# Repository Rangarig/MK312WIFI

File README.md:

# MK312 Wifi Bridge

This Project is a replacement for the bluetooth module used on the MK312BT and is based on the ESP8266-01S. This was created at first because the bluetooth interface could not be accessed in a convenient way on a VR headset, but also because of a general lack of reliability of the link. As usual no guarantees can be given, and also if you use this to injure yourself, no responsibility can be taken. This project is a collaboration between Rangarig and cLx. Some code has been imported back from [timdev](https://github.com/timduru/MK312WIFI/commits/timdev/) branch.

## Contents
| Directory      | Contains
|----------------|-------------------------------------------------------------------------|
| MK312Wifi      | Firmware that should be used to flash the ESP (ino source and bin file) |
| MK312-wifi-pcb | Schematics and board KiCad files needed to produce the PCB              |
| DotNetClient   | Example implementation in .net (visual studio code)                     |

## General
This WiFi interface is pin to pin compatible to the bluetooth interface, and designed to be an easier way to make custom implementations of the communication with the MK312 powerbox.
Included is an example C# implementation, that can be used in a unity project. Most existing implementations should be really easy to adapt to this WiFi version.

To make things configuration free the firmware replies to specific broadcast UDP packet, so the software can automatically determine the IP address of the interface.
A single TCP port is used for the actual communication with the device. At any time, only one client can be connected. You can also use the web interface for simple control.

You can see a connection by the radio LED lighting up and then flashing as communication is in progress.

## Hardware
Feel free to use the provided PCB layout for the connections. In case you want to build your own:
Keep in mind that the VCC from the box is 5 volts, so you will need to convert that to 3.3V or you will burn your ESP module.
The signal level from the box is already at 3.3 volts (as there is already a resistor bridge) so we don't really need to do anything else.

Connections are:

| ESP Pin Name | In-between            | MK312 |
|--------------|-----------------------|-------|
| GND          |                       | GND   |
| VCC          | 3.3V regulator        | VCC   |
| CHIP_EN      |                       |       |
| GPIO0        |                       | TX    |
| GPIO2        |                       | RX    |
| GPIO1        | NPN transistor        | STATE |
| GPIO3        | AP mode switch to GND |       |

The hardware serial port outputs a lot of garbage in the bootloader, that can confuse the MK312, so a software implementation is used that might make the used pin seem a bit odd.

## Firmware
Upon first powerup, the device will go into an Access Point mode (the MK312 display will show "WifiAP"), and you can connect to with your cellphone to configure the connection to your local wifi network. Once a WiFi connection is established, the device will display the IP obtained IP address on the LCD display. In consequent powerups the device will reconnect to the same wifi network. If you wish to change the network to use, press the config wifi button. The WifiAP mode is also automatically called if the configured network is not found after power up.

The firmware will negotiate a key with the box, and then use that key continuously internally.
You can send a UDP broadcast to port 8842 containing the string "MK312-ICQ" to have the device return its IP address.
You can then create a TCP connection to that IP Address on port 8843.

### Normal encrypted mode:
you can then proceed just like you would with a serial connection, and send the 0x00 to recieve 0x07 and then do the key negotation
### Unencrypted mode:
if you wish to skip encryption, instead of the normal key negotiation command you need to send `0x2f4242`. This is an invalid checksum, but the command will be recognized by the device.
It will reply with `0x69`. From there on you do not need to use any encryption.

From here on communication is no different from the serial communication:
https://docs.buttplug.io/docs/stpihkal/protocols/erostek-et312b/

Serial software implementations should not notice the difference. Once connection is lost, the software should be able to reestablish the connection normaly.

## Building

Please note that not all components need to be fitted to the front of the device. There are hints on PCB to what goes where.

|Qty| Component                 |
|---|---------------------------|
| 1 | ESP8266-01S module        |
| 1 | AMS1117-3.3 regulator     |
| 2 | 100nF (104) capacitors    |
| 1 | 2N2222 transistor         |
| 1 | Tactile switch 6x6 mm     |
| 1 | 5 pins pin header, angled |
| 1 | 2x4 pins socket, angled   |

## Flashing the firmware

Please keep in mind that the ESP8266-01 runs on 3.3 volts. So your serial adapter should be set in **3.3 VOLTS MODE** or the ESP will die.
The ESP8266-01 can be programmed connected like this:

|Row 1|Pins|Row 2|
|-----|----|-----|
|  TX |o  o| GND |
|  EN |o  o|     |
| RST |o  o| PRG |
|3.3V |o  o| RX  |

(ESP module top view, row 1 is closer to its board edge)

To put the ESP into programming mode, keep IO0/PRG connected to ground. You can make RST touch GND briefly to force a reset (it is possible to use the RTS output of the USB serial adapter to do this automatically, but most of the time, this is not needed).

Once the ESP is programmed and attached to the board you can put it into the MK312 bluetooth slot, please make sure its facing the right way.

Once the ESP Powers up, it will immediately try to negotiate with the MK312. If that fails, it will show an error message on the message LED:

| Number of blinks | Cause                                |
|------------------|--------------------------------------|
| 1                | Invalid checksum                     |
| 2                | Handshake failed at step 1           |
| 3                | Handshake failed at step 2           |
| 4                | Handshake failed at step 3           |
| 5                | Unexpected reply from device         |
| 10               | Unexpected reply from poke operation |
| 11               | Unexpected reply from peek operation |

Once negotiations are successful, the WIFI module will power up. On first startup it will go into AP mode.
Look for a network called 'MK312CONFIG-AP' and connect to it with your cellpone. Then set up the WIFI Parameters.
The module will then connect to WIFI, and display its IP adress on the MK312's display.
At this point it is ready to be connected to. The network settings are saved to be used automatically the next time the box is switched on.

### Flashing the provided bin files:
```
$ esptool --chip esp8266 --port /dev/ttyUSB0 --baud 115200 write_flash 0x0 MK312Wifi.ino.bin
esptool.py v3.0
Serial port /dev/ttyUSB0
Connecting....
Chip is ESP8266EX
Features: WiFi
Crystal is 26MHz
Uploading stub...
Running stub...
Stub running...
Configuring flash size...
Compressed 363184 bytes to 258186...
Wrote 363184 bytes (258186 compressed) at 0x00000000 in 22.9 seconds (effective 126.8 kbit/s)...
Hash of data verified.
```

Then the same for the webserver files, the difference is the destination address:

```
$ esptool --chip esp8266 --port /dev/ttyUSB0 --baud 115200 write_flash 0xEB000 MK312Wifi.mklittlefs.bin
```

(If you have installed the Arduino software, esptool can also be called with `python3 ~/.arduino15/packages/esp8266/hardware/esp8266/3.1.2/tools/esptool/esptool.py`)

### Compiling and flashing from the source code with the Arduino software:
Setting up the Arduino software: (it might work with newer versions, these are just the versions we developed things on)
Install Arudino: https://www.arduino.cc/en/software (Version 1.8.19)
Install Boardmanager: http://arduino.esp8266.com/stable/package_esp8266com_index.json (Version 3.0.2) [Generic ESP8266 module]
(under 'file/preferences' add the path to "Additional Boards Manager URLs:", then close the dialog with okay, and select the board on "Tools / boardmanager")
Install WifiManager: https://github.com/tzapu/WifiManager (version 2.0.5-beta)
(Download the file, and add it to your libraries with Sketch/Include Library/Add. Zip library)

Then close the application, reopen it and load the ino file.

HTTP and websocket servers feature need files under data/ to be uploaded on the ESP module. You can add [this tool](https://github.com/earlephilhower/arduino-esp8266littlefs-plugin/releases) in the Arduino interface.

Once all is setup correctly, you should be able to compile the accompanied .ino and flash it to the device.

## Usage

### Using software implemented for it:
There is no configuration necessary. The software will determine the IP via UDP broadcast and then connect to it.

List of implementations follows:
  - See the example C# application
  - https://github.com/clxjaguar/mk312-gui (PyQt GUI supporting cable link and unencrypted or legacy network links)

### Using legacy cable or bluetooth software:
There is software able to make a virtual serial port, which any software using serial port use.
#### Linux:
In linux you can use socat to establish a connection to the device, and offer a comport for the legacy software to connect to.
The syntax is as follows (replace [] with the corresponding values):

`socat -v pty,link=/home/[user]/tcptty0,raw tcp:[IP Address shown on display]:8843`

Then, you can then connect to `/home/[user]/tcptty0` from your software.

#### Windows:
VSPE (Virtual Serial Port Emulator) is known to work pretty well.
https://www.youtube.com/watch?v=7g6v_m208LQ

### Using the web and websocket interface:
There is a websocket server running on port 81, for simple control. Message format is `<command>=<argument>`. A HTTP webserver on port 80 is also serving html/css/js page using it, but also responding to GET requests `/EXEC?cmd=<command>&val=<argument>` or `/RAW?cmd=<address>&val=<byte>`.

Implemented commands are:

| Command     | Argument                                    |
|-------------|---------------------------------------------|
| Mode        | 0x76 to 0x8e for the differents modes       |
| DisableADC  | 1 to override pots, 0 to reenable them      |
| EnableADC   | 1 to restore pots, 0 to override them       |
| LevelA      | 0 to 255 (DisableADC=1 is needed before)    |
| LevelB      | 0 to 255 (same)                             |
| startRamp   | No argument needed for this command         |
| CutLevels   | 1 to set both channels levels to zero       |
| MultiAdjust | 0 to 100 (scaled in the current mode range) |

## Bonus picture of a MK312 with the v1.1 WiFi bridge interface in the grass

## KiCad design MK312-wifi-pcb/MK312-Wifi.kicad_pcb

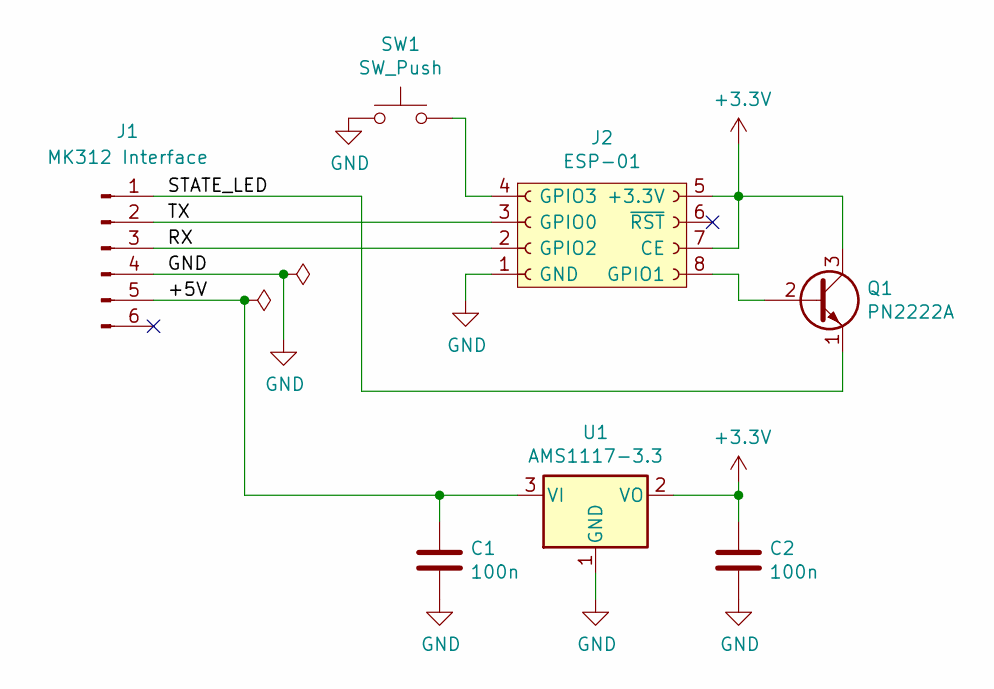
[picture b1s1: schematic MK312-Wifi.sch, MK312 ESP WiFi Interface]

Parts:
C1, C2: 100n; C_Disc_D4.7mm_W2.5mm_P5.00mm
J1: MK312 Interface; Pin_Header_Angled_1x06_Pitch2.54mm
J2: ESP-01; ESP_2x04
Q1: PN2222A; TO-92_Molded_Wide_Oval
SW1: SW_Push; SW_PUSH_6mm
U1: AMS1117-3.3; SOT-223-3_TabPin2

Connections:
+3V3: C2.1, J2.5 (+3.3V), J2.7 (CE), Q1.3 (C), U1.2 (VO)
/+5V: C1.1, J1.5, U1.3 (VI)
/RX: J1.3, J2.2 (GPIO2)
/STATE_LED: J1.1, Q1.1 (E)
/TX: J1.2, J2.3 (GPIO0)
GND: C1.2, C2.2, J1.4, J2.1 (GND), SW1.1, U1.1 (GND)
unnamed: J2.4 (GPIO3), SW1.2
unnamed: J2.8 (GPIO1), Q1.2 (B)

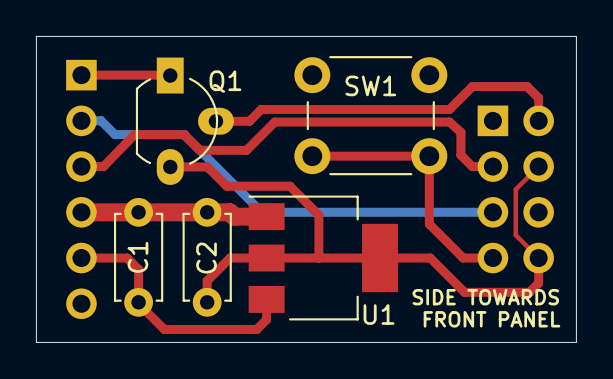
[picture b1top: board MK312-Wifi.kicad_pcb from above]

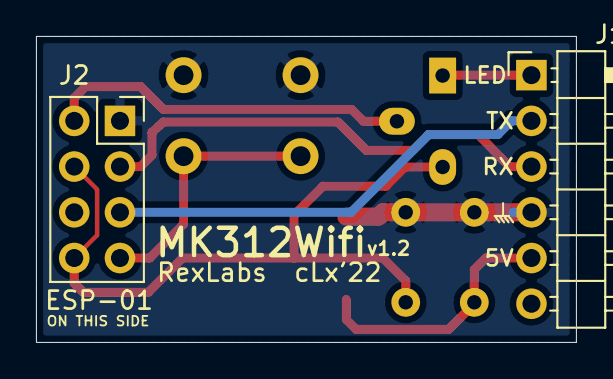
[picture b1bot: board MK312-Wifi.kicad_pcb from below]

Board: 2 copper layers, 30.0 x 17.0 mm, 7 parts (2 on the bottom side), 8 nets.

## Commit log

2022-11-26 Updated the C# Example code so its easier to read / integrate with other projects
2022-11-27 Moved the communication functionality into its own library, for even easier integration with other projects.
2022-11-27 VS File Cleanup
2023-01-11 Fix: removed Udp.flush() as it was just sending a second reply packet (but empty)
2023-03-02 Fixed a couple of warning message caused by a missing "const" keyword.
    MK312Wifi.ino: In function 'void configModeCallback(WiFiManager*)':
    MK312Wifi.ino:156:13: warning: ISO C++ forbids converting a string constant to 'char*' [-Wwrite-strings]
    156 | writeText("WifiAP");
    | ^~~~~~~~
    MK312Wifi.ino: In function 'void checkForAP()':
    MK312Wifi.ino:227:17: warning: ISO C++ forbids converting a string constant to 'char*' [-Wwrite-strings]
2023-03-02 Removed some commented code, and fixed some others comments and whitespaces
2023-03-02 Fixed a possible buffer overflow when obtained IP is displayed at power-on
    MK312Wifi.ino: In function 'void setup()':
    MK312Wifi.ino:215:14: warning: 'sprintf' may write a terminating nul past the end of the destination [-Wformat-overflow=]
    215 | sprintf(s, ">%i.%i.%i.%i", ip[0],ip[1],ip[2],ip[3]);
    | ^~~~~~~~~~~~~~
    MK312Wifi.ino:215:10: note: 'sprintf' output between 9 and 17 bytes into a destination of size 16
    215 | sprintf(s, ">%i.%i.%i.%i", ip[0],ip[1],ip[2],ip[3]);
2023-03-02 Changed: macros are in capitals letters, and "Udp" is changed to "udp" becChanged: macros are in capitals letters, and "Udp" is changed to "udp" because classes names begins by a capital, instantiate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
2023-03-02 Unused variables removal
2023-03-02 "wifiEncryption" flag's type changed from int to bool, changed version number to 1.2.01
2023-03-26 Implemented serial communication option for people who do not have the wifi adapter. Fixed a bug with setting the encryption key
2023-03-26 Attempted cleanup of binaries
2024-04-08 Removal of old commentated code and extra useless blank spaces
2024-04-08 Removed all occurences of "client.flush()" because as the client.setNoDelay(true) statement, making any individual write() sending the TCP packet immediately (see https://arduino-esp8266.readthedocs.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
2024-04-08 Fixing the code to send multi-bytes responses in only one packet (and not one packet per byte). Advancing version number to 1.2.01
2024-04-08 Added firmware binary ready to be flashed, version 1.2.02
2024-04-09 BOM update (diode was used in the v1.1, replaced by a transistor in the v1.2)
2024-04-09 Documentation update (cont'd...)
2024-04-10 Updated README.md with pictures and schematics
2024-04-10 Update README.md again...
2024-04-11 Small change of a comment
2024-05-23 Added: v1.2 PCB fabrication files (gerbers and drl)
2024-07-07 Giving to the mk312 more time to boot up (10ms -> 200ms)
2024-07-07 Removal of several useless flush() and adding a very, very useful one
2024-07-08 Lots of cosmetic fixes
2024-07-08 Make the "radio" status LED to blink better in activity ; ensures it is off once disconnected ; and very short flashes when replying to UDP beacons
2024-07-08 wiFiServer.available() is deprecated and renamed to accept()
2024-07-08 Delegates the checksum validity to the client application (make MK312Wifi easier to debug, passed hours because of old SoftwareSerial library and 0xFF messages terminations)
2024-07-08 Advance version number to 1.2.03, updating binary build file
2024-07-28 Fix a warning (-Wunused-parameter) in the WiFiManager callback. Nobody cares about this but me...
2024-07-28 Version 1.2.04: new feature: web and websocket servers (based on Tim's work, commit cda5ba4f39ef414446961b29e30c3949d98c5ffb)
2024-07-28 Added: Files for the integrated webserver (data/), based on cda5ba4f39ef414446961b29e30c3949d98c5ffb)
2024-07-29 Documentation update
2024-08-05 Config button: "OnDemandAP" SSID is renamed as "MK312CONFIG-AP" (using AP_NAME macro)
2024-08-05 Fix: when pressing on the config button, stopping webservers before starting OnDemandAP WifiManager menu
2024-08-05 Advance version number to 1.2.05, updating binary build file
2025-02-18 Some modification to handleLedBlinking()
2025-02-18 Little script I use to automate the flashing process
2025-02-18 Improved Websocket access embedded webpage. Now we're into the future!
